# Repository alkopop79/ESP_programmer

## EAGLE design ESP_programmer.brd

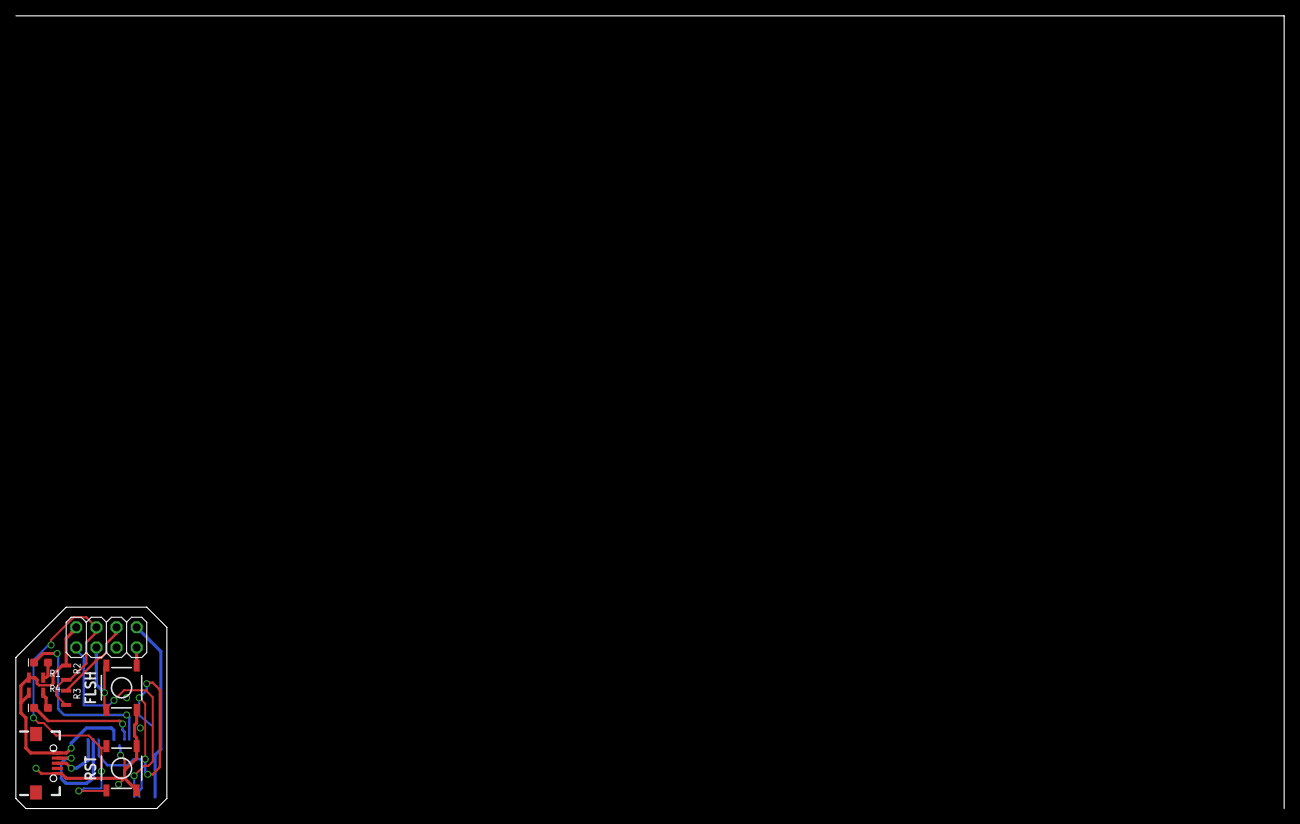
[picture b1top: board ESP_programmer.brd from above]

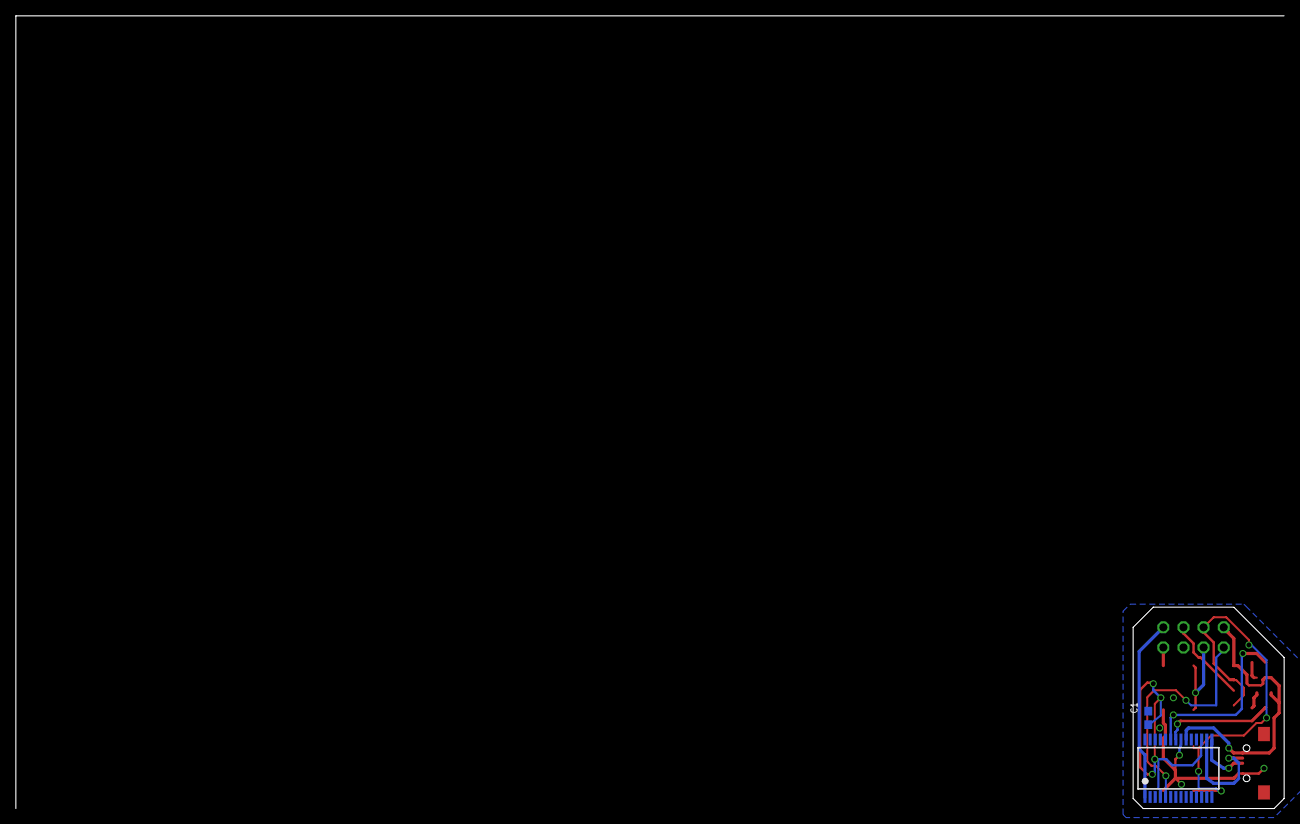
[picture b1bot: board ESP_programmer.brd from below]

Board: 2 copper layers, 19.1 x 25.4 mm, 12 parts (2 on the bottom side), 14 nets.

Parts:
C1: 100nF; 0603
D1: TX; LED-0603
D2: RX; LED-0603
FLSH: MOMENTARY-SWITCH-SPST-SMD-5.2-REDUNDANT; TACTILE_SWITCH_SMD_5.2MM
IC1: FT232RL; SSOP28
JP1: 2X04
R1, R4: 270; MINI_MELF-0102R
R2, R3: 10k; MINI_MELF-0102R
RST: MOMENTARY-SWITCH-SPST-SMD-5.2-REDUNDANT; TACTILE_SWITCH_SMD_5.2MM
U1: USB-MICRO-SMD

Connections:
CH_PD: JP1.6, R3.1
GPIO0: FLSH.1, FLSH.2, JP1.3
unnamed: D2.A, R4.1
unnamed: IC1.16, U1.D-1
unnamed: IC1.15, U1.D+1
unnamed: D1.A, R1.1
unnamed: C1.1, IC1.4, IC1.17
unnamed: D1.C, IC1.23
unnamed: D2.C, IC1.22
RST: JP1.4, R2.2, R3.2, RST.1, RST.2
TXD: IC1.1, JP1.8
V+: IC1.20, JP1.2, R1.2, R2.1, R4.2, U1.VBUS1
V-: C1.2, FLSH.3, FLSH.4, IC1.7, IC1.18, IC1.21, IC1.25, IC1.26, JP1.7, RST.3, RST.4, U1.GND1
\: IC1.5, JP1.1

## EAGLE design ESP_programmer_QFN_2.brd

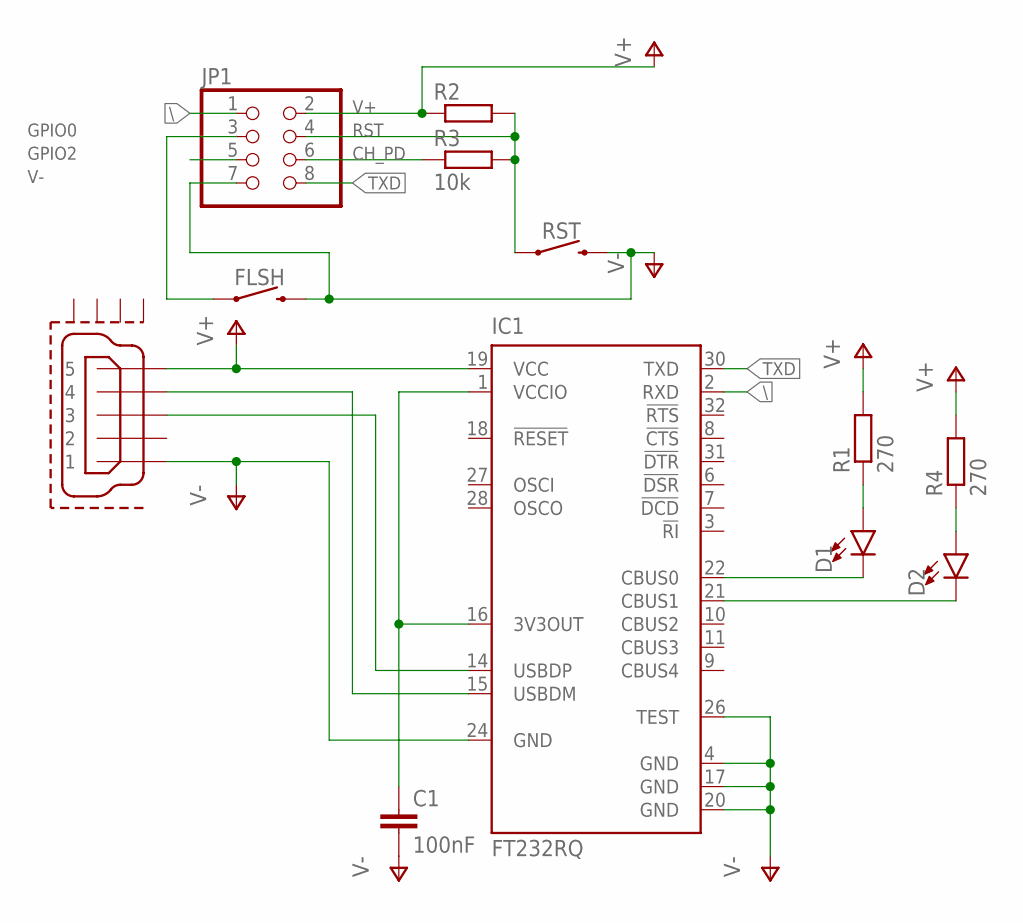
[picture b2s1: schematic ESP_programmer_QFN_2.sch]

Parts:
C1: 100nF; C1608
D1: TX; LED-0603
D2: RX; LED-0603
FLSH: MOMENTARY-SWITCH-SPST-SMD-5.2-REDUNDANT; TACTILE_SWITCH_SMD_5.2MM
IC1: FT232RQ; QFN32
JP1: PINHD-2X4; 2X04
R1, R4: 270; R2012
R2, R3: 10k; R2012
RST: MOMENTARY-SWITCH-SPST-SMD-5.2-REDUNDANT; TACTILE_SWITCH_SMD_5.2MM
U1: MICRO-USB-RECEPTACLE47589-0001; 47589-0001

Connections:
CH_PD: JP1.6, R3.1
GPIO0: FLSH.1, FLSH.2 (1), JP1.3
GPIO2: JP1.5
unnamed: D2.A, R4.1
unnamed: IC1.15 (USBDM), U1.4
unnamed: IC1.14 (USBDP), U1.3
unnamed: D1.A, R1.1
unnamed: C1.1, IC1.1 (VCCIO), IC1.16 (3V3OUT)
unnamed: D1.C, IC1.22 (CBUS0)
unnamed: D2.C, IC1.21 (CBUS1)
RST: JP1.4, R2.2, R3.2, RST.1, RST.2 (1)
TXD: IC1.30 (TXD), JP1.8
V+: IC1.19 (VCC), JP1.2, R1.2, R2.1, R4.2, U1.5
V-: C1.2, FLSH.3 (2), FLSH.4 (2), IC1.4 (GND), IC1.17 (GND), IC1.20 (GND), IC1.24 (GND), IC1.26 (TEST), JP1.7, RST.3 (2), RST.4 (2), U1.1
\: IC1.2 (RXD), JP1.1

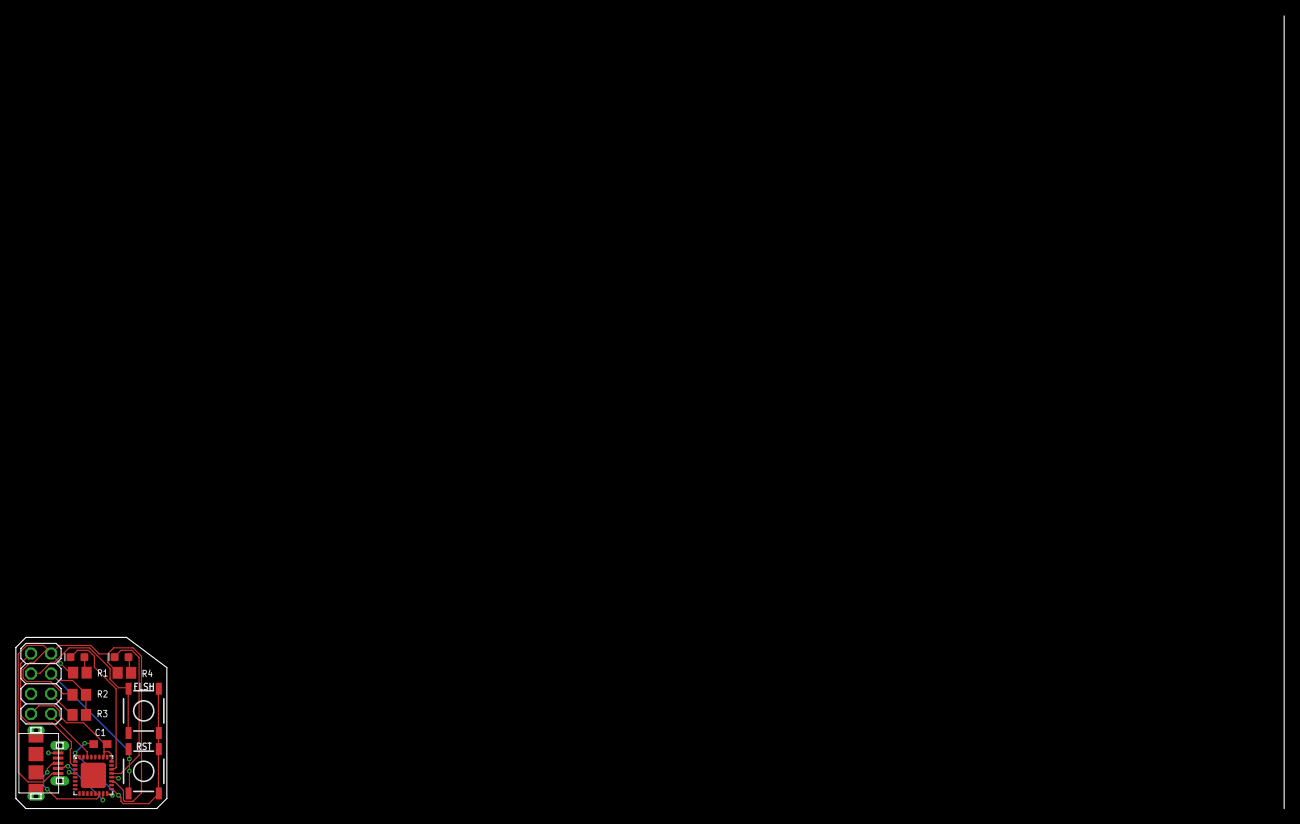
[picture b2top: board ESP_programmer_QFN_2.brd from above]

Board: 2 copper layers, 19.1 x 21.6 mm, 12 parts (0 on the bottom side), 14 nets.

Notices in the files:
parts and their libraries:
SparkFun-Capacitors: Licensing: Creative Commons ShareAlike 4.0 International - https://creativecommons.org/licenses/by-sa/4.0
con-molex-usb: (C) 2014 Tomasz Boleslaw CEDRO, cederom@tlen.pl, http://www.tomek.cedro.info.
